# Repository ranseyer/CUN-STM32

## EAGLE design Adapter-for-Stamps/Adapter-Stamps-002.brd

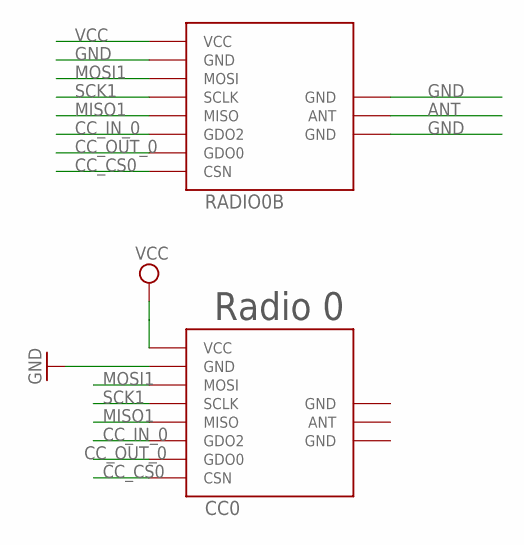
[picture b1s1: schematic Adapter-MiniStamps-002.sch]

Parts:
CC0: CC1101_MODULE1SMD; CC1101_MODULE1_SMD
RADIO0B: CC1101_MODULE1SMALL; CC1101_MODULE1_SMD

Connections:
ANT: RADIO0B.ANT; also elsewhere on the board
CC_CS0: CC0.CSN, RADIO0B.CSN; also elsewhere on the board
CC_IN_0: CC0.GDO2, RADIO0B.GDO2; also elsewhere on the board
CC_OUT_0: CC0.GDO0, RADIO0B.GDO0; also elsewhere on the board
GND: CC0.GND@0 (GND), RADIO0B.GND@0 (GND), RADIO0B.GND@1 (GND), RADIO0B.GND@2 (GND); also elsewhere on the board
MISO1: CC0.MISO, RADIO0B.MISO; also elsewhere on the board
MOSI1: CC0.MOSI, RADIO0B.MOSI; also elsewhere on the board
SCK1: CC0.SCLK, RADIO0B.SCLK; also elsewhere on the board
VCC: CC0.VCC, RADIO0B.VCC; also elsewhere on the board

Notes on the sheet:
Radio 0

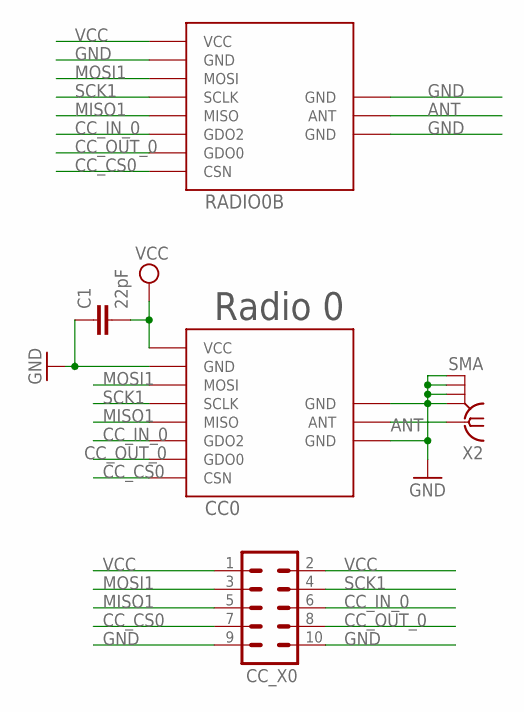
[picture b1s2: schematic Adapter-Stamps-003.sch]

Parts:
C1: 22pF; C0805
CC0: CC1101_MODULE1SMD; CC1101_MODULE1_SMD
CC_X0: MA05-2
RADIO0B: CC1101_MODULE1SMALL; CC1101_MODULE1_SMD
X2: SMA

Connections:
ANT: CC0.ANT, RADIO0B.ANT, X2.1
CC_CS0: CC0.CSN, CC_X0.7, RADIO0B.CSN
CC_IN_0: CC0.GDO2, CC_X0.6, RADIO0B.GDO2
CC_OUT_0: CC0.GDO0, CC_X0.8, RADIO0B.GDO0
GND: C1.1, CC0.GND@0 (GND), CC0.GND@1 (GND), CC0.GND@2 (GND), CC_X0.9, CC_X0.10, RADIO0B.GND@0 (GND), RADIO0B.GND@1 (GND), RADIO0B.GND@2 (GND), X2.GND@1 (2), X2.GND@2 (3), X2.GND@3 (4), X2.GND@4 (5)
MISO1: CC0.MISO, CC_X0.5, RADIO0B.MISO
MOSI1: CC0.MOSI, CC_X0.3, RADIO0B.MOSI
SCK1: CC0.SCLK, CC_X0.4, RADIO0B.SCLK
VCC: C1.2, CC0.VCC, CC_X0.1, CC_X0.2, RADIO0B.VCC

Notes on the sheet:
Radio 0

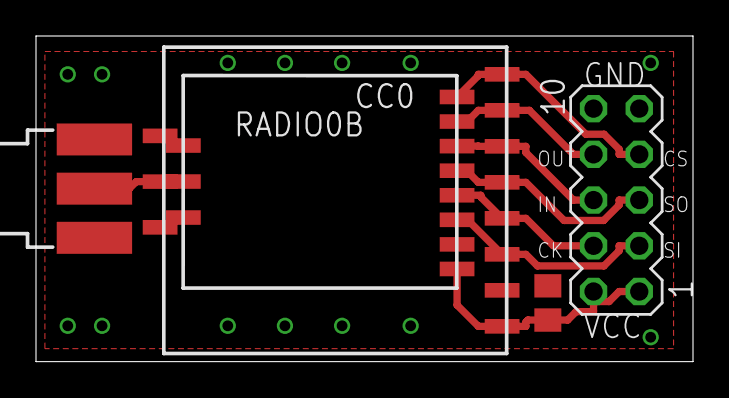
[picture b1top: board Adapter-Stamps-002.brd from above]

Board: 2 copper layers, 36.5 x 18.1 mm, 5 parts (0 on the bottom side), 9 nets.

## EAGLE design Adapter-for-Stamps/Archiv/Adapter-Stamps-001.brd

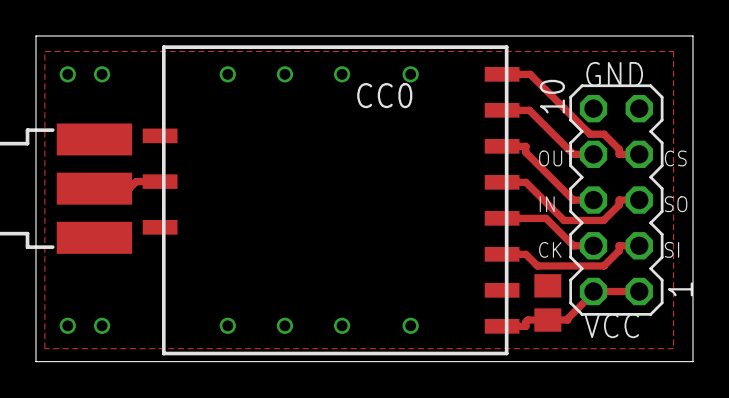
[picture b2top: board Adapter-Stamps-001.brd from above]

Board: 2 copper layers, 36.5 x 18.1 mm, 4 parts (0 on the bottom side), 9 nets.

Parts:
C1: 22pF; C0805
CC0: CC1101_MODULE1SMD; CC1101_MODULE1_SMD
CC_X0: MA05-2
X2: SMA

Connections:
CC_CS0: CC0.CSN, CC_X0.7
CC_IN_0: CC0.GDO2, CC_X0.6
CC_OUT_0: CC0.GDO0, CC_X0.8
GND: C1.1, CC0.GND@0, CC0.GND@1, CC0.GND@2, CC_X0.9, CC_X0.10, X2.GND@1, X2.GND@2, X2.GND@3, X2.GND@4
MISO1: CC0.MISO, CC_X0.5
MOSI1: CC0.MOSI, CC_X0.3
unnamed: CC0.ANT, X2.1
SCK1: CC0.SCLK, CC_X0.4
VCC: C1.2, CC0.VCC, CC_X0.1, CC_X0.2

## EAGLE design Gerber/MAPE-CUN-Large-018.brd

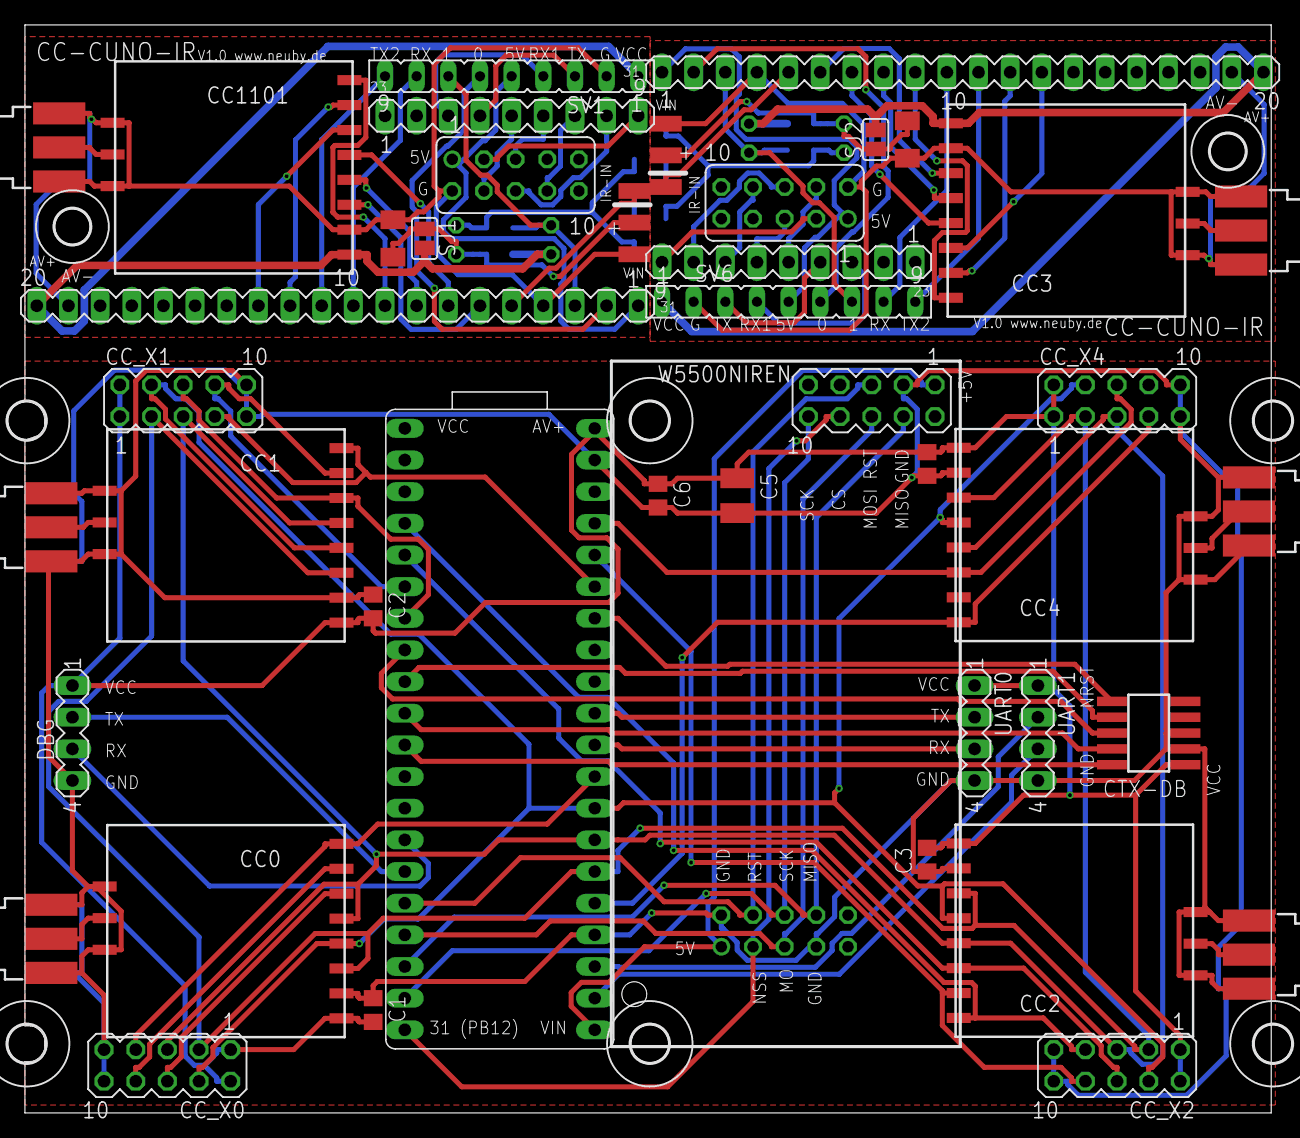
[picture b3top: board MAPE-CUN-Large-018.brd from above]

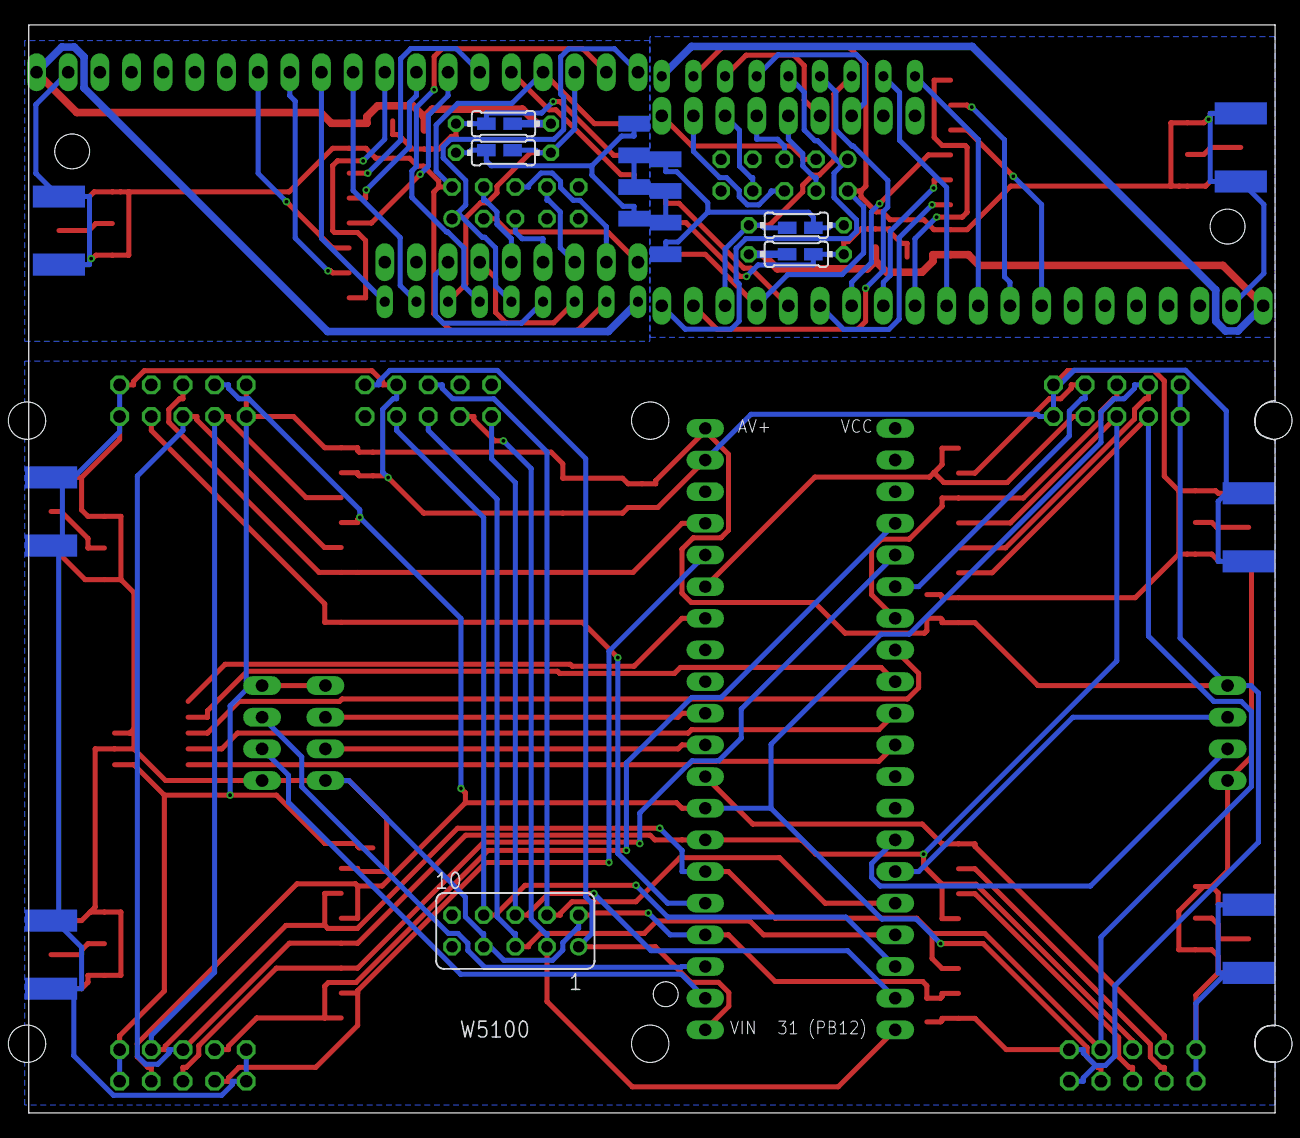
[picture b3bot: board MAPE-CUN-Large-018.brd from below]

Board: 2 copper layers, 100.0 x 87.3 mm, 71 parts (17 on the bottom side), 87 nets.

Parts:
C1, C2, C3, C4, C6: 22pF; C0805
C5: 10uF; C1210
C7, C8: 4,7uF; C1206K
CC0, CC1, CC2, CC3, CC4, CC1101: CC1101_MODULE1SMD; CC1101_MODULE1_SMD
CC_X0, CC_X1, CC_X2, CC_X4: MA05-2
CTX-DB: 1365-10
DBG: MA04-1
GND, GND1: SMD1,27-2,54
H1, H2, H3, H4, H5, H6: MOUNT-HOLE3.0; 3,0
H7, H8: MOUNT-HOLE2.8; 2,8
IR+, IR+1: SMD1,27-2,54
IR-IN, IR-IN1: SMD1,27-2,54
PC+, PC+1: SMD1,27-2,54
PC-, PC-1: SMD1,27-2,54
PWR+, PWR+1: SMD1,27-2,54
PWR-, PWR-1: SMD1,27-2,54
R1, R2: 100; 0204/7
R3, R4: 100; R0805W
R5, R6: 220; 0204/7
R7, R8: 220; R0805W
SJ1, SJ2: SJ
SV1, SV6: FE09
SV2, SV4: MA20-1
SV3, SV5: MA09-1
U$1: MAPLEMINI; 20-DIP
UART0, UART1: MA04-1
W1, W2, W5100: FE05-2
W5500NIREN: MA05-2
X1, X2, X3, X4, X5, X6: SMA

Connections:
0-PB1: SV2.2, SV6.6
0-PB11: SV1.6, SV4.2
1-PB1: R6.1, R8.1, SV2.3, SV6.7
1-PB10: R5.1, R7.1, SV1.7, SV4.3
3-PB0: IR-IN.1, SV4.5
3-PB1: IR-IN1.1, SV2.5
+5V: U$1.21, W5100.1, W5500NIREN.1
+5V1: SV1.5, SV4.1, W1.1
+5V2: SV2.1, SV6.5, W2.1
CC_CS0: CC0.CSN, CC_X0.7, U$1.29
CC_CS1: CC1.CSN, CC_X1.7, U$1.35
CC_CS2: CC2.CSN, CC_X2.7, U$1.4
CC_CS3: CC4.CSN, CC_X4.7, U$1.25
CC_IN_0: CC0.GDO2, CC_X0.6
CC_IN_1: CC1.GDO2, CC_X1.6, U$1.7
CC_IN_2: CC2.GDO2, CC_X2.6, U$1.5
CC_IN_3: CC4.GDO2, CC_X4.6, U$1.37
CC_IN_4: CC1101.GDO2, SV4.13
CC_IN_5: CC3.GDO2, SV2.13
CC_OUT_0: CC0.GDO0, CC_X0.8
CC_OUT_1: CC1.GDO0, CC_X1.8, U$1.6
CC_OUT_2: CC2.GDO0, CC_X2.8, U$1.36
CC_OUT_3: CC1101.GDO0, SV4.12
CC_OUT_4: CC3.GDO0, SV2.12
CSN: CC1101.CSN, SV4.9
CSN1: CC3.CSN, SV2.9
GND: C1.1, C2.1, C3.1, C4.1, C5.2, C6.2, CC0.GND@0, CC0.GND@1, CC0.GND@2, CC1.GND@0, CC1.GND@1, CC1.GND@2, CC2.GND@0, CC2.GND@1, CC2.GND@2, CC4.GND@0, CC4.GND@1, CC4.GND@2, CC_X0.9, CC_X0.10, CC_X1.9, CC_X1.10, CC_X2.9, CC_X2.10, CC_X4.9, CC_X4.10, CTX-DB.3, CTX-DB.5, DBG.4, U$1.24, U$1.39, UART0.4, UART1.4, W5100.2, W5100.7, W5500NIREN.3, X1.GND@1, X1.GND@2, X1.GND@3, X1.GND@4, X2.GND@1, X2.GND@2, X2.GND@3, X2.GND@4, X3.GND@1, X3.GND@2, X3.GND@3, X3.GND@4, X4.GND@1, X4.GND@2, X4.GND@3, X4.GND@4
GND1: C7.2, CC1101.GND@0, CC1101.GND@1, CC1101.GND@2, GND.1, SV1.2, SV4.4, SV4.19, W1.2, X5.GND@1, X5.GND@2, X5.GND@3, X5.GND@4
GND2: C8.2, CC3.GND@0, CC3.GND@1, CC3.GND@2, GND1.1, SV2.4, SV2.19, SV6.2, W2.2, X6.GND@1, X6.GND@2, X6.GND@3, X6.GND@4
IR+: C7.1, IR+.1, R2.1, R3.1, SJ1.1
IR+1: C8.1, IR+1.1, R1.1, R4.1, SJ2.1
MISO1: CC0.MISO, CC1.MISO, CC2.MISO, CC4.MISO, CC_X0.5, CC_X1.5, CC_X2.5, CC_X4.5, U$1.27
MISO2: U$1.18, W5100.8, W5500NIREN.4
MISO3: SV5.7, W1.8
MISO4: SV3.7, W2.8
MOSI: CC1101.MOSI, SV4.6
MOSI1: CC0.MOSI, CC1.MOSI, CC2.MOSI, CC4.MOSI, CC_X0.3, CC_X1.3, CC_X2.3, CC_X4.3, U$1.26
MOSI2: SV5.6, W1.5
MOSI3: CC3.MOSI, SV2.6
MOSI4: SV3.6, W2.5
unnamed: CC2.ANT, X3.1
unnamed: CC4.ANT, X4.1
unnamed: CC1.ANT, X1.1
unnamed: CC0.ANT, X2.1
unnamed: CC1101.ANT, X5.1
unnamed: CC1101.MISO, SV4.7
unnamed: CC1101.SCLK, SV4.8
unnamed: CC3.ANT, X6.1
unnamed: CC3.MISO, SV2.7
unnamed: CC3.SCLK, SV2.8
NRESET: CTX-DB.10, U$1.34
PWR+: PC+.1, PWR+.1, R5.2, R7.2
PWR+1: PC+1.1, PWR+1.1, R6.2, R8.2
PWR-: PC-.1, PWR-.1
PWR-1: PC-1.1, PWR-1.1
RST: U$1.17, W5100.5, W5500NIREN.6
RX0: U$1.30, UART0.3
RX1: U$1.22, UART1.3
RX2: SV1.4, SV5.3
RX3: SV3.3, SV6.4
RX_DBG: DBG.3, U$1.14
S2RX: SV1.8, SV4.10
S2RX1: SV2.10, SV6.8
S2TX: SV1.9, SV4.11
S2TX1: SV2.11, SV6.9
SCK1: CC0.SCLK, CC1.SCLK, CC2.SCLK, CC4.SCLK, CC_X0.4, CC_X1.4, CC_X2.4, CC_X4.4, U$1.28
SCK2: U$1.19, W5100.6, W5500NIREN.10
SCK3: SV5.8, W1.6
SCK4: SV3.8, W2.6
SWCLK/TCK: CTX-DB.4, U$1.10
SWDIO/TMS: CTX-DB.2, U$1.11
SWO/TDO: CTX-DB.6, U$1.8
TDI: CTX-DB.8, U$1.9
TX0: U$1.31, UART0.2
TX1: U$1.23, UART1.2
TX2: SV1.3, SV5.4
TX3: SV3.4, SV6.3
TX_DBG: DBG.2, U$1.15
VCC: C1.2, C2.2, C3.2, C4.2, C5.1, C6.1, CC0.VCC, CC1.VCC, CC2.VCC, CC4.VCC, CC_X0.1, CC_X0.2, CC_X1.1, CC_X1.2, CC_X2.1, CC_X2.2, CC_X4.1, CC_X4.2, CTX-DB.1, DBG.1, U$1.40, UART0.1, UART1.1
VCC1: CC1101.VCC, R2.2, R3.2, SJ1.2, SV1.1, SV4.20
VCC2: CC3.VCC, R1.2, R4.2, SJ2.2, SV2.20, SV6.1
WIZ_CS: U$1.20, W5100.3, W5500NIREN.8
WIZ_CS1: SV5.9, W1.3
WIZ_CS2: SV3.9, W2.3
WIZ_RST: U$1.16, W5100.4, W5500NIREN.5
WIZ_RST1: SV5.5, W1.4
WIZ_RST2: SV3.5, W2.4

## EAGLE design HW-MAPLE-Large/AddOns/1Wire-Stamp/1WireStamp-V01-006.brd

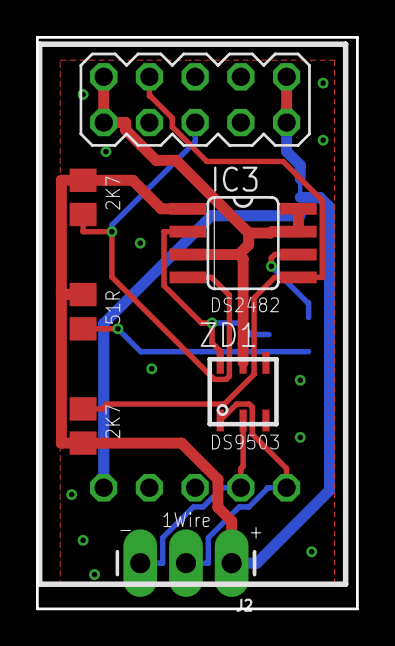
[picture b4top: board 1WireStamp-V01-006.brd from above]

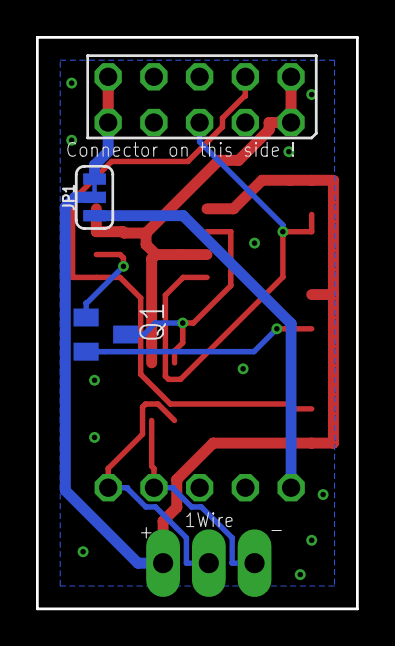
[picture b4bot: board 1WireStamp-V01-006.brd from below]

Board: 2 copper layers, 17.8 x 31.8 mm, 9 parts (2 on the bottom side), 11 nets.

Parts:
CC2-EXT: ONEWIRE-MODULEONEWIRE_CC1101_WO-SILK; ONEWIRE_CC1101_MOD_WO_SILK
IC3: DS2482; SO08
J2: 1X03_LONGPADS
JP1: JUMPER-SMT_3_1-NC_TRACE_SILK; SMT-JUMPER_3_1-NC_TRACE_SILK
Q1: BSS84; SOT23
R1: 2k7; R0805
R2: 2K7; R0805
R4: 51; R0805
ZD1: DS9503P; TSOC6

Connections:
1W: CC2-EXT.1W, J2.2, ZD1.1
1W-GND: CC2-EXT.1W-GND, J2.3, ZD1.2
CC_CS2: CC2-EXT.CSN, IC3.5, R1.2
CC_IN_2: CC2-EXT.GDO2, IC3.4, R2.2
GND: CC2-EXT.GND@0, CC2-EXT.GND@1, IC3.3, IC3.7, IC3.8, ZD1.5
unnamed: IC3.6, Q1.1
unnamed: IC3.2, Q1.3, ZD1.6
unnamed: Q1.2, R4.1
V1W: IC3.1, J2.1, JP1.2, R1.1, R2.1, R4.2
VCC: CC2-EXT.VCC@0, CC2-EXT.VCC@1, JP1.3
VIN: CC2-EXT.5, JP1.1

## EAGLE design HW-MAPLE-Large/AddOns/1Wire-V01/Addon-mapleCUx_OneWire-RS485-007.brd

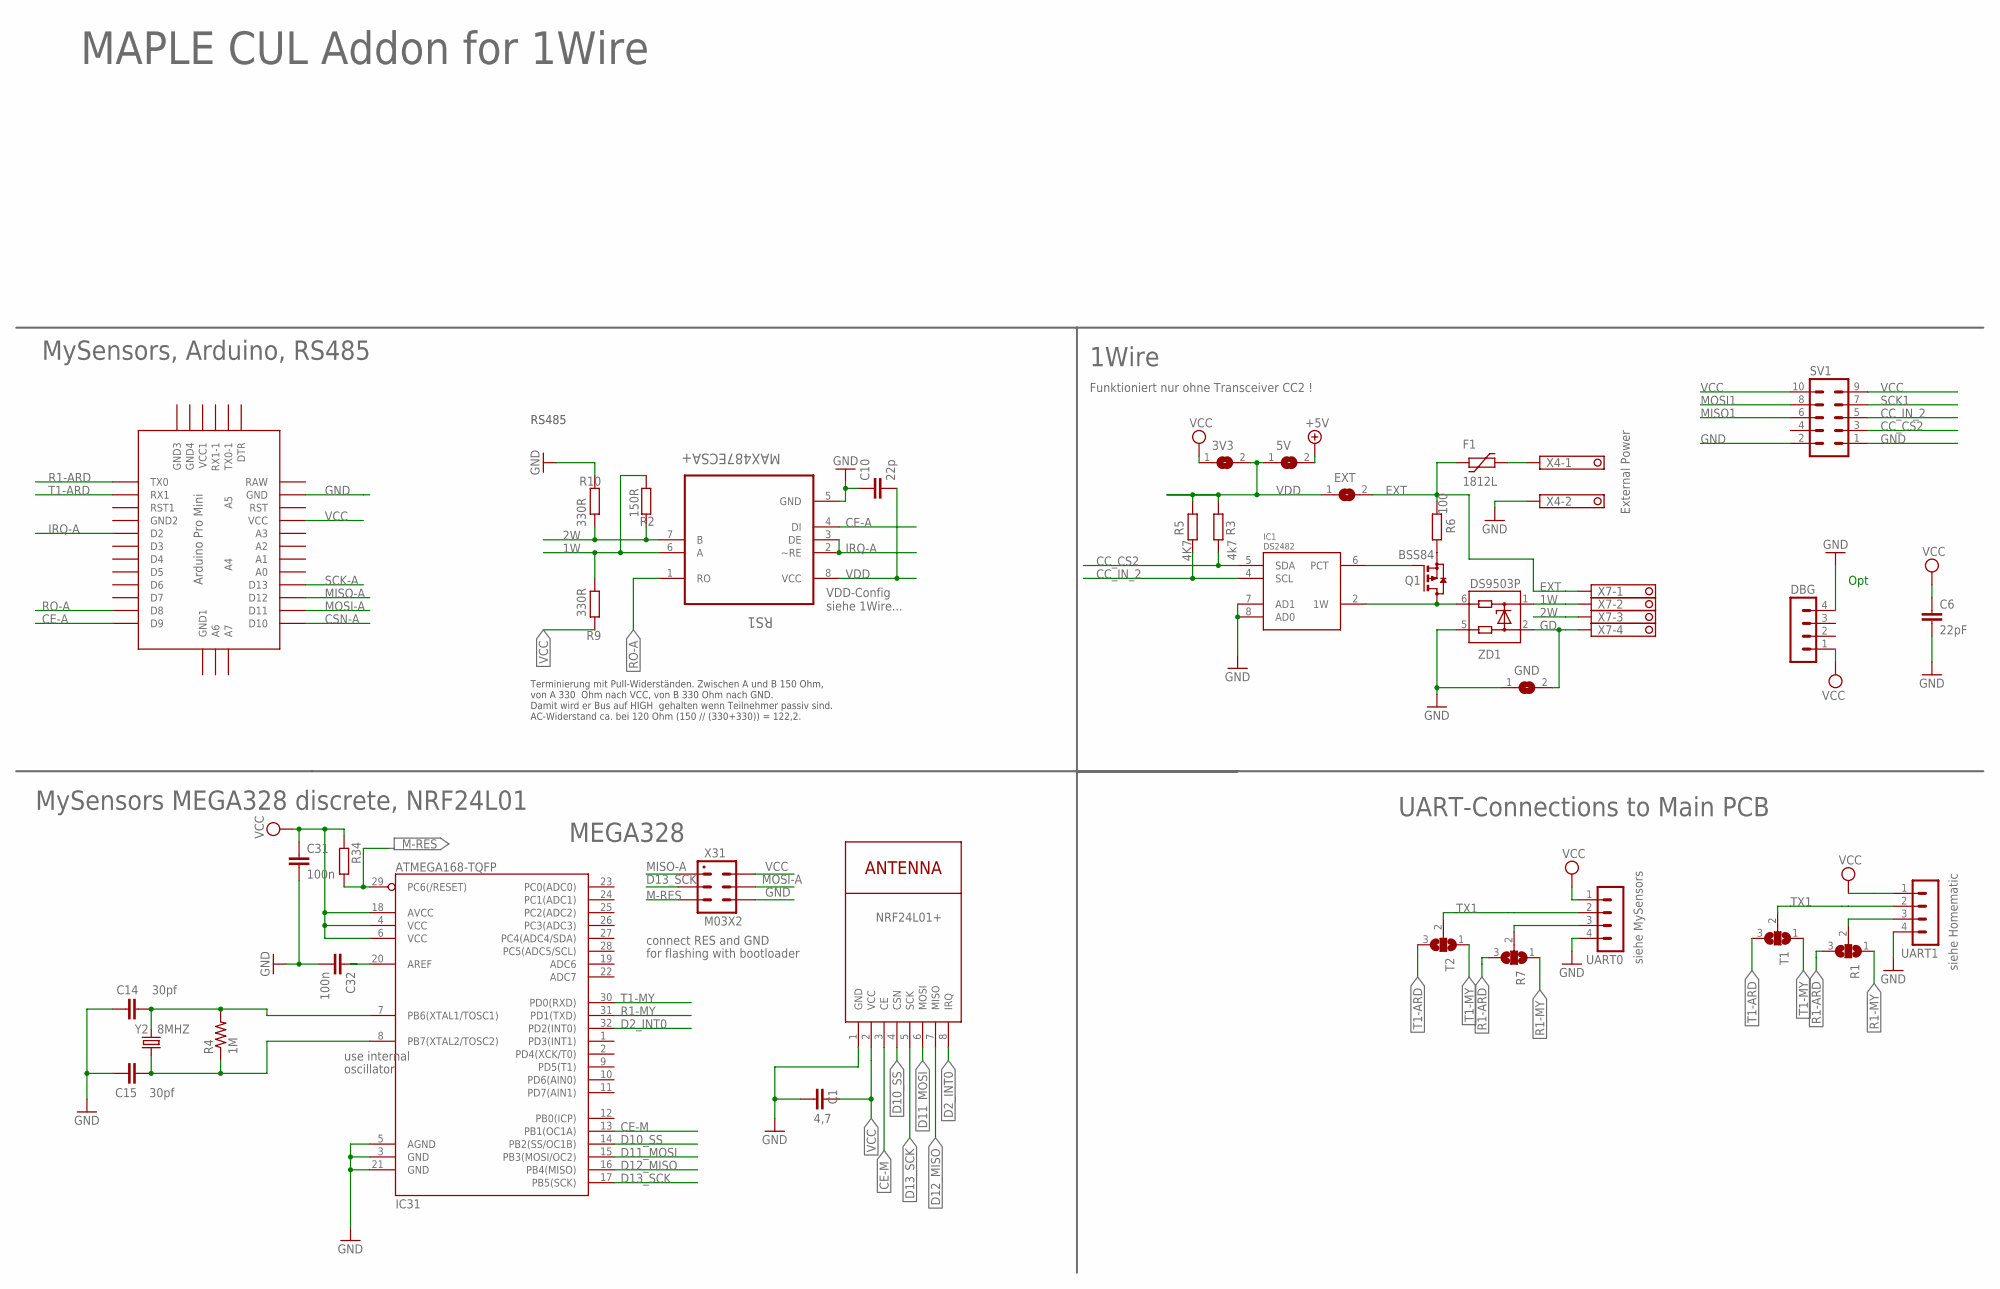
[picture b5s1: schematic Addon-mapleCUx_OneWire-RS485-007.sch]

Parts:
3V3, 5V: SJ
C1: 4,7; C1210
C6: 22pF; C0805
C10: 22p; C0805
C14, C15: 30pf; 0805
C31, C32: 100n; C0805
DBG: MA04-1
EXT: SJ
F1: 1812L
GND: SJ
IC1: DS2482; SO08
IC31: ATMEGA168-TQFP; TQFP32-08
NRF24L01+: NRF24L01+; WIRELESS-NRF24L01
Q1: BSS84; SOT23
R1, R7: SJ2W; SJ_2
R2: 150R; R0805
R3: 4k7; R0805
R4: 1M; 0805
R5: 4K7; R0805
R6: 100; R0805
R9, R10: 330R; R0805
R34: R-EU_R0805; R0805
RS1: MAX487ECSA+; SOIC127P600X175-8N
SV1: MA05-2
T1, T2: SJ2W; SJ_2
U$1: ABK-PRO-MINI
UART0, UART1: MA04-1
X4: 1751248
X7: 1751264
X31: M03X2; 2X03-1.27MM_SMD
Y2: 8MHZ; CRYSTAL-TXC-7A
ZD1: DS9503P; TSOC6

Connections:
1W: R2.1, R9.2, RS1.6 (A), X7.2, ZD1.1
2W: R2.2, R10.1, RS1.7 (B), X7.3
+5V: 5V.2
CC_CS2: IC1.5 (SDA), R3.2, SV1.3
CC_IN_2: IC1.4 (SCL), R5.2, SV1.5
CE-A: RS1.4 (DI), U$1.D9
CE-M: IC31.13 (PB1(OC1A)), NRF24L01+.3 (CE)
CSN-A: U$1.D10
D2_INT0: IC31.32 (PD2(INT0)), NRF24L01+.8 (IRQ)
D10_SS: IC31.14 (PB2(SS/OC1B)), NRF24L01+.4 (CSN)
D11_MOSI: IC31.15 (PB3(MOSI/OC2)), NRF24L01+.6 (MOSI)
D12_MISO: IC31.16 (PB4(MISO)), NRF24L01+.7 (MISO)
D13_SCK: IC31.17 (PB5(SCK)), NRF24L01+.5 (SCK), X31.P$3 (3)
EXT: EXT.2, F1.P$1 (1), R6.2, X7.1
GD: GND.2, X7.4, ZD1.2
GND: C1.1, C6.2, C10.1, C14.1, C15.1, C31.2, C32.2, DBG.4, GND.1, IC1.3 (GND), IC1.7 (AD1), IC1.8 (AD0), IC31.3 (GND), IC31.5 (AGND), IC31.21 (GND), NRF24L01+.1 (GND), R10.2, RS1.5 (GND), SV1.1, SV1.2, U$1.GND, UART0.4, UART1.4, X4.2, X31.P$6 (6), ZD1.5
IRQ-A: RS1.2 (~RE), RS1.3 (DE), U$1.D2
M-RES: IC31.29 (PC6(/RESET)), R34.2, X31.P$5 (5)
MISO1: SV1.6
MISO-A: U$1.D12, X31.P$1 (1)
MOSI1: SV1.8
MOSI-A: U$1.D11, X31.P$4 (4)
unnamed: C14.2, IC31.7 (PB6(XTAL1/TOSC1)), R4.2, Y2.P$2 (2)
unnamed: C32.1, IC31.20 (AREF)
unnamed: C15.2, IC31.8 (PB7(XTAL2/TOSC2)), R4.1, Y2.P$1 (1)
unnamed: F1.P$2 (2), X4.1
unnamed: IC1.6 (PCT), Q1.1 (G)
unnamed: IC1.2 (1W), Q1.3 (D), ZD1.6
unnamed: Q1.2 (S), R6.1
R1-ARD: R1.3, R7.3, U$1.TX0
R1-MY: IC31.31 (PD1(TXD)), R1.1, R7.1
RO-A: RS1.1 (RO), U$1.D8
RX1: R1.2, R7.2, UART0.3, UART1.3
SCK1: SV1.7
SCK-A: U$1.D13
T1-ARD: T1.3, T2.3, U$1.RX1
T1-MY: IC31.30 (PD0(RXD)), T1.1, T2.1
TX1: T1.2, T2.2, UART0.2, UART1.2
VCC: 3V3.1, C1.2, C6.1, C31.1, DBG.1, IC31.4 (VCC), IC31.6 (VCC), IC31.18 (AVCC), NRF24L01+.2 (VCC), R9.1, R34.1, SV1.9, SV1.10, U$1.VCC, UART0.1, UART1.1, X31.P$2 (2)
VDD: 3V3.2, 5V.1, C10.2, EXT.1, IC1.1 (VDD), R3.1, R5.1, RS1.8 (VCC)

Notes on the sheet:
Opt
siehe Homematic
siehe MySensors
MySensors MEGA328 discrete, NRF24L01
MEGA328
use internal
oscillator
connect RES and GND
for flashing with bootloader
1Wire
External Power
Funktioniert nur ohne Transceiver CC2 !
MySensors, Arduino, RS485
RS485
VDD-Config siehe 1Wire...
Terminierung mit Pull-Widerständen. Zwischen A und B 150 Ohm, von A 330 Ohm nach VCC, von B 330 Ohm nach GND. Damit wird er Bus auf HIGH gehalten wenn Teilnehmer passiv sind. AC-Widerstand ca. bei 120 Ohm (150 // (330+330)) = 122,2.
UART-Connections to Main PCB
MAPLE CUL Addon for 1Wire

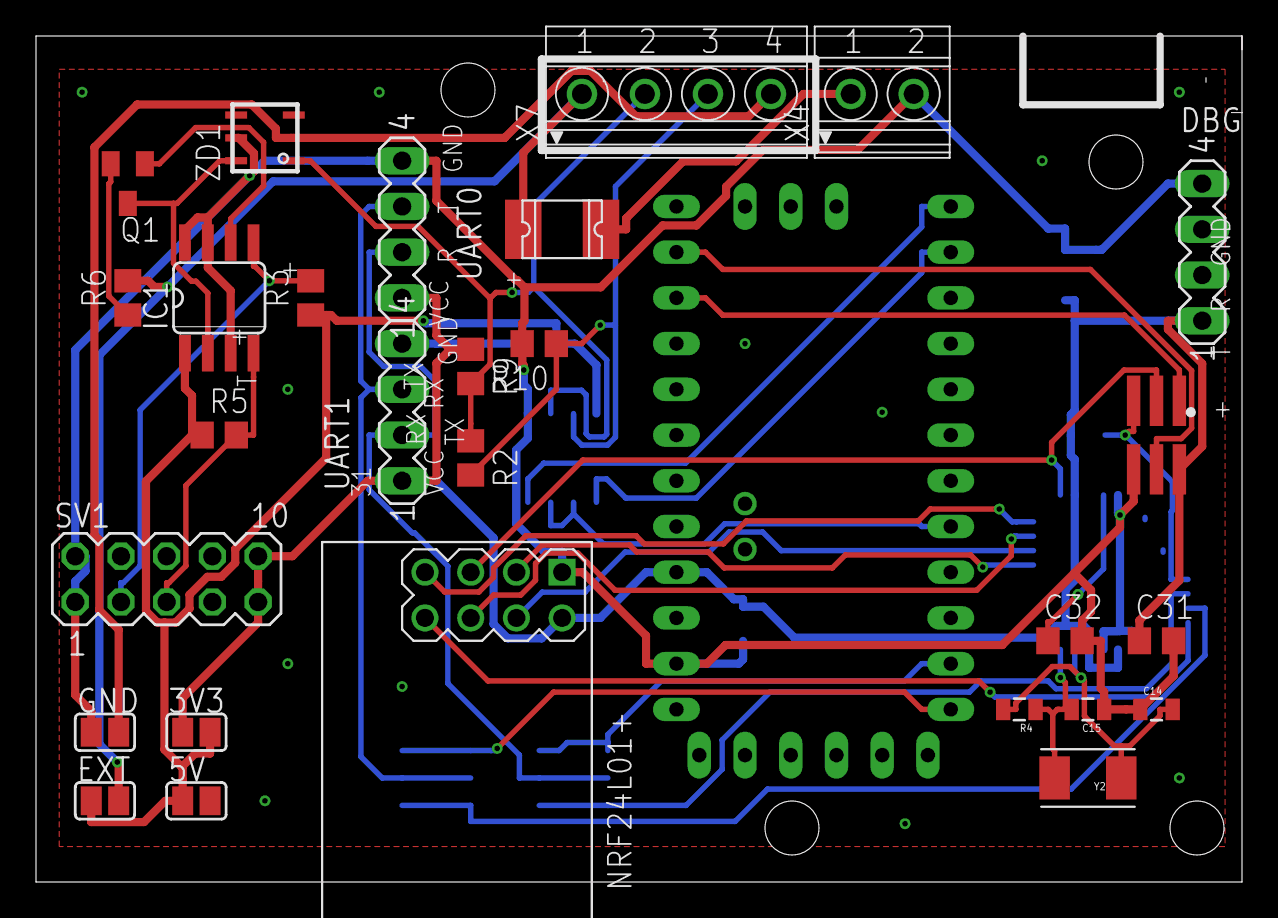
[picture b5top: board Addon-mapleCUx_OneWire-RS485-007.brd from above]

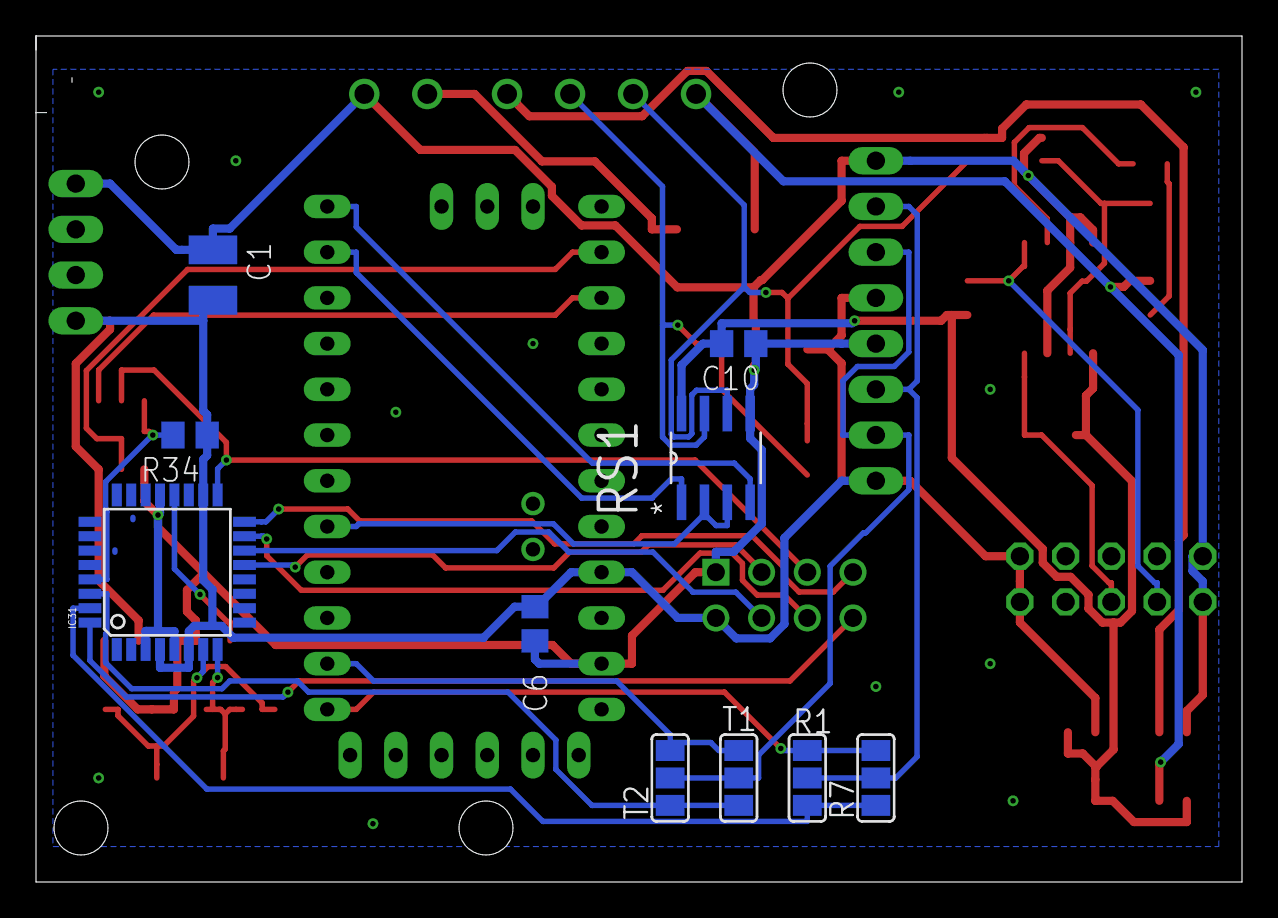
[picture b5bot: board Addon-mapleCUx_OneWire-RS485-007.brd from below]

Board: 2 copper layers, 67.0 x 47.0 mm, 39 parts (10 on the bottom side), 34 nets.

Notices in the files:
parts and their libraries:
SparkFun-Jumpers: Licensing: Creative Commons ShareAlike 4.0 International - https://creativecommons.org/licenses/by-sa/4.0
diy-modules: Released under the Creative Commons Attribution 4.0 International License: http://creativecommons.org/licenses/by/4.0
